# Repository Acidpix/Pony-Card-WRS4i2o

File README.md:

# Pony-Card-WRS4i2o

Pony-Card-WRS4i2o is a Wiegand/RS485 capable card for access controle powered by PoE

# Main feature 
  - Powered by PoE or 12V/2A input
  - Power sercurity device like badge reader in 12V/0.5A
  - Wiegand or RS485 input selectable by switch
  - In Wiegand mode, 1 digital output (e.g for drive 5V Led or buzzer from badge reader)   
  - 4 digital input (3V to 24V)
  - Drive 2 output NO/NC relay (230V/5A Max)
  - Can run on WiFi and/or Ethernet (e.g for failover)
  - Ready to Home assistant with EspHOME (Sample config avaliable)
  - Ready to MQTT with Tasmota (Base firmware avaliable)
  - -20C° +60C° running continous capability
  - Fit in DIN PLC Box like [this](https://fr.aliexpress.com/i/1005004933689728.html)
  - Dimention : 92.4mm X 87.5  

# Esp32 Pin Mapping 
  - GPIO 0 : Flash write mode Conected to CH340
  - GPIO 1 : UART_TX Conected to CH340
  - GPIO 2 : Free use in pin header
  - GPIO 3 : UART_RX Conected to CH340
  - GPIO 4 : Free use in pin header
  - GPIO 5 : Free use in pin header
  - GPIO 6 - 11 : Reserved by flash memory
  - GPIO 12 : Ethernet PHY Power
  - GPIO 13 : Wiegand D0 or RS485 RX
  - GPIO 14 : Wiegand D1 or RS485 TX
  - GPIO 15 : RS485 DIR or digital out in Wiegand mode (e.g for drive status LED on badge reader)
  - GPIO 16 : Free use in pin header
  - GPIO 17 : EMAC Clock out 180
  - GPIO 18 : MDIO(RMII)
  - GPIO 19 : EMAC TXD0(RMII)
  - GPIO 21 : EMAC TX Enable
  - GPIO 22 : EMAC TXD1(RMII)
  - GPIO 23 : MDC(RMII)
  - GPIO 25 : EMAC RXD0(RMII)
  - GPIO 26 : EMAC RXD1(RMII)
  - GPIO 27 : EMAC RX CRS DV
  - GPIO 32 : Relay 1
  - GPIO 33 : Relay 2
  - GPIO 34 : Digital Input 1 (3V - 24V)
  - GPIO 35 : Digital Input 2 (3V - 24V)
  - GPIO 36 : Digital Input 3 (3V - 24V)
  - GPIO 39 : Digital Input 4 (3V - 24V)

# Wiegand ESPHome example 

``` 
esphome:
  name: Pony Card WRS4i2o
  friendly_name: Pony_Card_WRS4i2o

esp32:
  board: esp32dev
  framework:
    type: arduino

# Enable logging
logger:

# Enable Home Assistant API
api:
  encryption:
    key: 

ota:
  password: 

ethernet:
  type: LAN8720
  mdc_pin: GPIO23
  mdio_pin: GPIO18
  clk_mode: GPIO17_OUT
  power_pin: GPIO12

globals:
  - id: autorized_badge
    type: int64_t
    restore_value: no
    initial_value: '5562314525698'

wiegand:
  - id: badgereader
    d0: GPIO13
    d1: GPIO14
    on_raw: 
      - if:
          condition:
            labda : 'return value == id(autorized_badge);
          then:
            - switch.toggle: r1
          else:
            - switch.toggle: r2
            - delay : 1s
            - switch.toggle: r2

binary_sensor:
  - platform: gpio
    pin: 
      number: 34
      inverted: true
    name: "input1"
  - platform: gpio
    pin: 
      number: 35
      inverted: true
    name: "input2"
  - platform: gpio
    pin: 
      number: 36
      inverted: true
    name: "input3"
  - platform: gpio
    pin: 
      number: 39
      inverted: true
    name: "input4"

output:
  - platform: gpio
    pin: 32
    id: 'Relay_1'  
  - platform: gpio
    pin: 33
    id: 'Relay_2'    

switch:
  - platform: output
    name: "Relay 1"
    id: "r1"
    output: 'Relay_1'
  - platform: output
    name: "Relay 2"
    id: "r2"
    output: 'Relay_2'
  - platform: gpio
    name: "LED"
    id: "led"
    pin:
      number: 15
      inverted: true 
``` 

# Misc
R49 was unpopulated resistance, because it's just for very old PoE device, support only type 1 PoE and this type need permanante 10mA current drain. But this produce 0.5w of heat and in certain condition make overhead the board, please populate only if your PoE injector dont work without an be careful of probaly over heating in +50C° environement.

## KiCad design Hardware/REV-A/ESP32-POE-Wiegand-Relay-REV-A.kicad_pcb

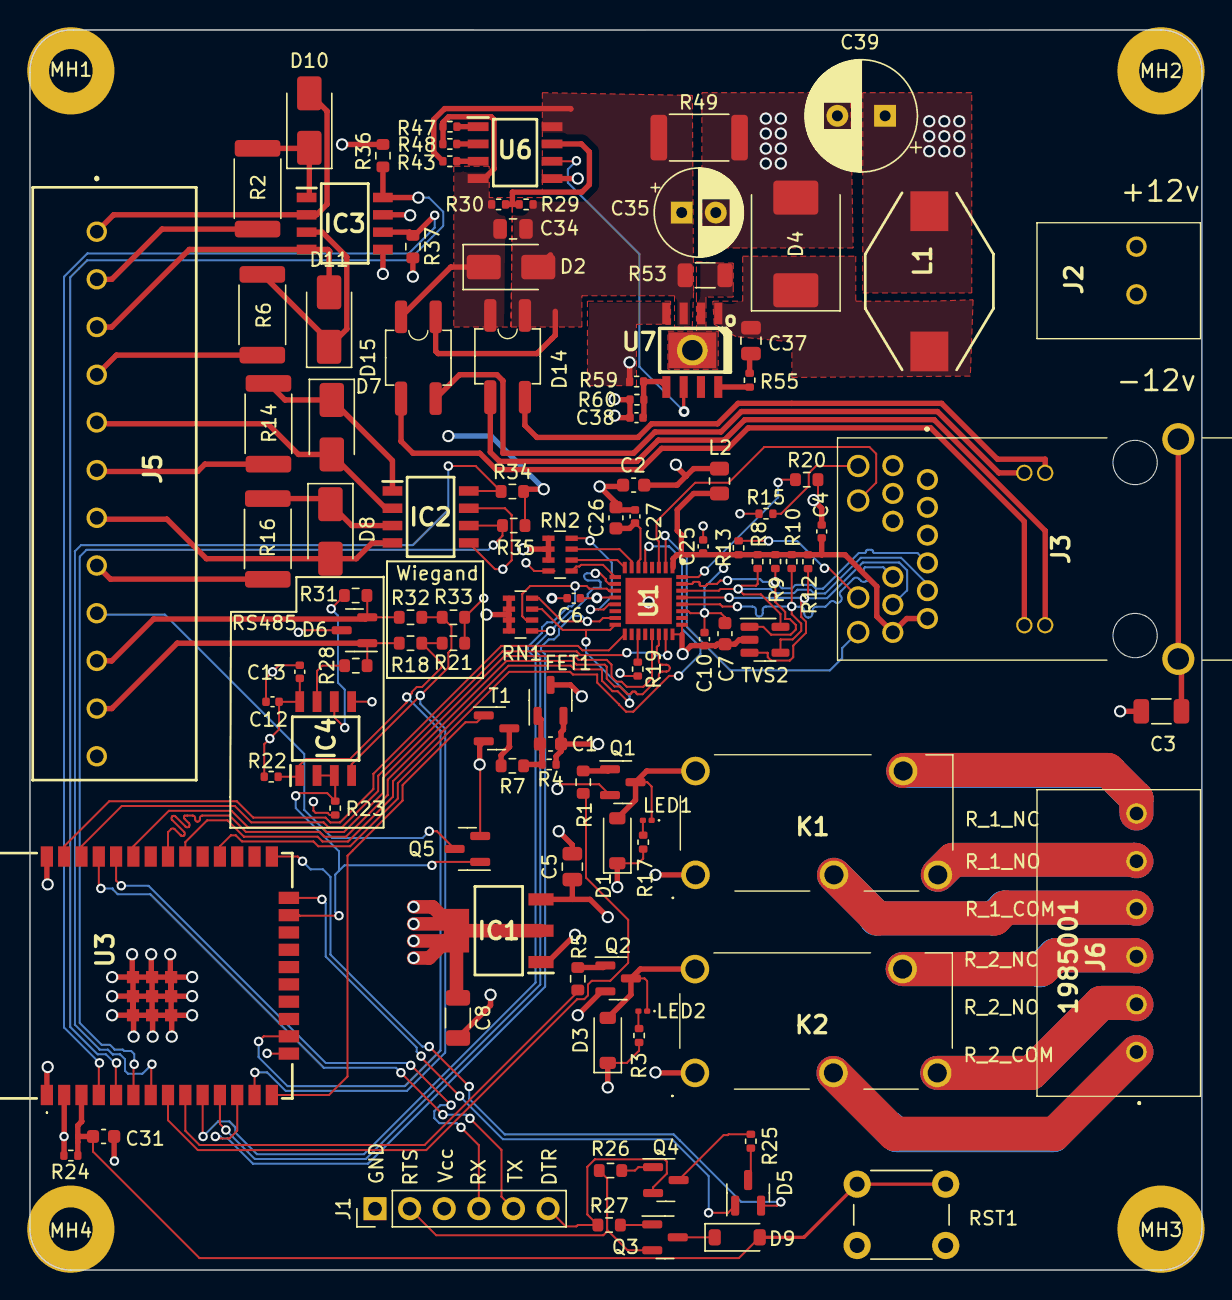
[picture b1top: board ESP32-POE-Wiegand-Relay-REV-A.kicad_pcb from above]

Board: 4 copper layers, 86.0 x 91.0 mm, 111 parts (0 on the bottom side), 99 nets.

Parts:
C1, C2, C7: 22uF/6.3V/20%/X5R/C0603; C_0603_1608Metric
C3: 1nF/2000V/10%/X7R/C1206; C_1206_3216Metric
C4, C6, C10, C12, C13, C25, C27: 100nF/16V/10%/X7R/C0402; C_0402_1005Metric
C5: 10uF/16v/10%/0805; C_0805_2012Metric
C8: 22uF/6.3v/10%/1206; C_1206_3216Metric
C26: 2.2uF/6.3V/10%/X5R/C0603; C_0603_1608Metric
C31: 1uF/10V/10%/X5R/C0603; C_0603_1608Metric
C34, C37: 100nF/100V/10%/X7R/C0805; C_0805_2012Metric
C35: 15uF/100V/20%/RM2.5/6.3x11mm(Farnell:1281844); CP_Radial_D6.3mm_P2.50mm
C38: 12pF/50V/5%/COG/C0402; C_0402_1005Metric
C39: 470uF/16V/20%/Low_ESR/RM3.5/8.0x15mm; CP_Radial_D8.0mm_P3.50mm
D1, D3, D9: 1N5819S4(SOD-123); D_SOD-123
D2: SMAJ58A/SMA; D_SMA
D4: SS510/100V/5A/0.85V/DO214AB(SMC); D_SMC
D5: BAT54C(SOT23-3); SOT-23
D6: STS232120B301; SOT-23
D7, D8, D10, D11: Diode 1KV; D_SMA
D14, D15: MDB10S YONG; SOP-4_3.8x4.1mm_P2.54mm_MB10S-YONG
FET1: WPM2015-3/TR; SOT-23-3
IC1: AZ1117CH-3.3TRG1; SOT230P700X180-4N
IC2, IC3: VOD207T; SOIC127P610X323-8N
IC4: THVD1420DR; SOIC127P600X175-8N
J1: Conn_01x06_MountingPin; PinHeader_1x06_P2.54mm_Vertical
J2: 1984963
J3: 0826-1X1T-GH-F; 08261X1TGHF
J5: 1985069
J6: 1985001
K1, K2: G5Q-1-DC12; G5Q1DC12
L1: DO3316P-333MLD; DO3316P333MLD
L2: FB0805/600R/2A; R_0805_2012Metric
LED1, LED2: LED/GREEN/0603; LED_0201_0603Metric
MH1, MH2, MH3, MH4: Mounting_hole_Shield_3.3mm; MountingHole_3.2mm_M3_Pad
Q1, Q2, Q3, Q4, Q5: BC817-40(SOT23); SOT-23
R1, R5, R7, R21, R26, R27, R33, R34, R35, R36, R37: 1k/R0603; R_0603_1608Metric
R2, R6, R14, R16: 1.2kR/5%/1W/2512/CR2512-JW-122ELF; R_2512_6332Metric
R3, R13, R15, R17: 2.2k/R0402; R_0402_1005Metric
R4, R19, R22, R23, R24, R30: 10k/R0402; R_0402_1005Metric
R8, R9, R10, R12: 49.9R/1%/R0402; R_0402_1005Metric
R18, R32: 470R/R0603; R_0603_1608Metric
R20: 12.1k/1%/R0603; R_0603_1608Metric
R25: 220R/R0402; R_0402_1005Metric
R28, R31: 10R/5%/pulse resistor/0603; R_0603_1608Metric
R29: 130k/R0402; R_0402_1005Metric
R43: 24.9k/1%/R0402; R_0402_1005Metric
R47: 180k/1%/R0402; R_0402_1005Metric
R48: 4.42k/1%/1/16W/R0402; R_0402_1005Metric
R49: 4.7k/R2512; R_2512_6332Metric
R53: 0.03R/1%/R1206; R_1206_3216Metric
R55: 4.7R/R0402; R_0402_1005Metric
R59: 21k/1%/R0402; R_0402_1005Metric
R60: 300k/1%/R0402; R_0402_1005Metric
RN1, RN2: 2.2k/5%/0603x4; R_Array_Concave_4x0603
RST1: T1107A(6x3,8x2,5MM); SW_PUSH_6mm
T1: LMUN2211LT1G(SOT-23); SOT-23
TVS2: ESDS314DBVR(SOT-23-5); SOT-23-5
U1: LAN8710A-EZC(QFN32); QFN50P500X500X100-33N-D
U3: ESP-WROOM-32; ESP32WROOM32EN4
U6: TPS2376DDAR-H (SO-8); SOIC127P600X175-8N
U7: TX4138(ESOIC-8); SOIC8E

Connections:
+3.3V: C1.1, C8.1, C12.2, C13.2, FET1.2, IC1.2 (OUTPUT), IC1.4 (VOUT), IC4.8 (VCC), J1.3, R4.1, R22.1, R24.1, R34.2, R35.2, R36.2, R37.2, U3.2 (3V3)
+3V3: C2.1, C6.1, FET1.3, L2.1, R19.2, RN1.5 (R4_2), RN1.6 (R3_2), RN1.7 (R2_2), RN1.8 (R1_2), RN2.8 (R1_2), U1.12 (VDDIO)
+12V: C5.1, C38.1, C39.1, D1.1 (K), D3.1 (K), IC1.3 (INPUT), J2.1, K1.1 (COIL_1), K2.1 (COIL_1), L1.2, R3.2, R17.2, R60.1
/+Input1: J5.8, R16.1
/+Input2: J5.6, R14.1
/+Input3: J5.4, R6.1
/+Input4: J5.2, R2.1
/-Input1: D8.2 (A), IC2.4 (C_2), J5.7
/-Input2: D7.2 (A), IC2.2 (C_1), J5.5
/-Input3: D11.2 (A), IC3.4 (C_2), J5.3
/-Input4: D10.2 (A), IC3.2 (C_1), J5.1
/D_Com: D5.3, R25.1
/ESP_EN: C31.2, D9.2 (A), R24.2, RST1.1, U3.3 (EN)
/GPI34/Input1: IC2.6 (C_3), R35.1, U3.6 (GPI34/ADC1_CH6/RTC_GPIO4)
/GPI35/Input2: IC2.8 (C_4), R34.1, U3.7 (GPI35/ADC1_CH7/RTC_GPIO5)
/GPI36/Input3: IC3.6 (C_3), R37.1, U3.4 (GPI36/SENSOR_VP/ADC_H/ADC1_CH0/RTC_GPIO0)
/GPI39/Input4: IC3.8 (C_4), R36.1, U3.5 (GPI39/SENSOR_VN/ADC1_CH3/ADC_H/RTC_GPIO3)
/GPIO0: D5.2, U3.25 (GPIO0/ADC2_CH1/TOUCH1/RTC_GPIO11/CLK_OU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)
/GPIO1/UART_TX0: J1.5, U3.35 (GPIO1/U0TXD/CLK_OUT3/EMAC_RXD2)
/GPIO2: D5.1, U3.24 (GPIO2/ADC2_CH2/TOUCH2/RTC_GPIO12/HSPIWP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)
/GPIO3/UART_RX0: J1.4, U3.34 (GPIO3/U0RXD/CLK_OUT2)
/GPIO12/PHY_PWR: T1.1 (B), U3.14 (GPIO12/ADC2_CH5/TOUCH5/RTC_GPIO15/MTDI/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)
/GPIO13/Wiegand_D0/RS485_RX: IC4.1 (R), R18.2, R21.2, R22.2, U3.16 (GPIO13/ADC2_CH4/TOUCH4/RTC_GPIO14/MTCK/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)
/GPIO14/Wiegand_D1/RS485_TX: IC4.4 (D), R32.2, R33.2, U3.13 (GPIO14/ADC2_CH6/TOUCH6/RTC_GPIO16/MTMS/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)
/GPIO15/Wiegand_LED/RS485_DIR: IC4.2 (~RE), IC4.3 (DE), Q5.1 (B), R23.1, U3.23 (GPIO15/ADC2_CH3/TOUCH3/MTDO/HSPICS0/RTC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)
/GPIO17/EMAC_CLK_OUT_180: U1.5 (XTAL1/CLKIN), U3.28 (GPIO17/HS1_DATA5/U2TXD/EMAC_CLK_OUT_180)
/GPIO18/MDIO(RMII): RN1.3 (R3_1), U1.16 (MDIO), U3.30 (GPIO18/VSPICLK/HS1_DATA7)
/GPIO19/EMAC_TXD0(RMII): U1.22 (TXD0), U3.31 (GPIO19/VSPIQ/U0CTS/EMAC_TXD0)
/GPIO21/EMAC_TX_EN(RMII): U1.21 (TXEN), U3.33 (GPIO21/VSPIHD/EMAC_TX_EN)
/GPIO22/EMAC_TXD1(RMII): U1.23 (TXD1), U3.36 (GPIO22/VSPIWP/U0RTS/EMAC_TXD1)
/GPIO23/MDC(RMII): U1.17 (MDC), U3.37 (GPIO23/VSPID/HS1_STROBE)
/GPIO25/EMAC_RXD0(RMII): RN1.2 (R2_1), U1.11 (RXD0/MODE0), U3.10 (GPIO25/DAC_1/ADC2_CH8/RTC_GPIO6/EMAC_RX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)
/GPIO26/EMAC_RXD1(RMII): RN1.1 (R1_1), U1.10 (RXD1/MODE1), U3.11 (GPIO26/DAC_2/ADC2_CH9/RTC_GPIO7/EMAC_RX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)
/GPIO27/EMAC_RX_CRS_DV: RN1.4 (R4_1), U1.15 (COL/CRS_DV/MODE2), U3.12 (GPIO27/ADC2_CH7/TOUCH7/RTC_GPIO17/EMAC_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)
/GPIO32/REL1: R1.1, U3.8 (GPIO32/XTAL_32K_P/ADC1_CH4/TOUCH9/RTC_G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)
/GPIO33/REL2: R5.1, U3.9 (GPIO33/XTAL_32K_N/ADC1_CH5/TOUCH8/RTC_G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)
/RD+: J3.4 (TRD2+), R9.1, TVS2.1 (I/O1), U1.31 (RXP)
/RD-: J3.5 (TRD2-), R8.1, TVS2.5 (I/O4), U1.30 (RXN)
/Relay_1_COM: J6.4, K1.2 (COM)
/Relay_1_NC: J6.6, K1.4 (NC)
/Relay_1_NO: J6.5, K1.3 (NO)
/Relay_2_COM: J6.1, K2.2 (COM)
/Relay_2_NC: J6.3, K2.4 (NC)
/Relay_2_NO: J6.2, K2.3 (NO)
/TD+: J3.11 (TRD1+), R12.1, TVS2.3 (I/O2), U1.29 (TXP)
/TD-: J3.10 (TRD1-), R10.1, TVS2.4 (I/O3), U1.28 (TXN)
/Wiegand_D0/RS485_A: D6.1 (K), J5.11, R18.1, R28.2
/Wiegand_D1/RS485_B: D6.2 (K), J5.10, R31.2, R32.1
/Wiegand_LED: J5.9, Q5.3 (C)
GND: C2.2, C3.1, C4.2, C5.2, C6.2, C7.2, C8.2, C10.2, C12.1, C13.1, C25.2, C26.2, C27.2, C31.1, C35.2, C39.2, D4.2 (A), D6.3 (A), IC1.1 (ADJ/GND), IC2.5 (E_1), IC2.7 (E_2), IC3.5 (E_1), IC3.7 (E_2), IC4.5 (GND), J1.1, J2.2, J5.12, MH1.1 (GND1), MH2.1 (GND1), MH3.1 (GND1), MH4.1 (GND1), Q1.2 (E), Q2.2 (E), Q5.2 (E), R15.2, R20.2, R21.1, R23.2, R33.1, R49.2, R59.2, RN2.5 (R4_2), RN2.6 (R3_2), RN2.7 (R2_2), RST1.2, T1.2 (E), TVS2.2 (GND), U1.24 (TXD2), U1.25 (TXD3), U1.33 (GND), U3.1 (GND), U3.15 (GND), U3.38 (GND), U3.39 (THERMAL_PAD), U3.40 (40_GND), U3.41 (41_GND), U3.42 (42_GND), U3.43 (43_GND), U3.44 (44_GND), U3.45 (45_GND), U3.46 (46_GND), U3.47 (47_GND), U6.5 (RTN), U7.4 (GND)
unnamed: C1.2, FET1.1, R4.2, R7.2
unnamed: C3.2, J3.MH1, J3.MH2
unnamed: C37.2, R55.2
unnamed: D1.2 (A), K1.5 (COIL_2), LED1.1 (K), Q1.3 (C)
unnamed: D3.2 (A), K2.5 (COIL_2), LED2.1 (K), Q2.3 (C)
unnamed: C37.1, D4.1 (K), L1.1, U7.1 (SW)
unnamed: D7.1 (K), IC2.1 (A_1), R14.2
unnamed: D8.1 (K), IC2.3 (A_2), R16.2
unnamed: D9.1 (K), Q3.3 (C)
unnamed: D10.1 (K), IC3.1 (A_1), R2.2
unnamed: D11.1 (K), IC3.3 (A_2), R6.2
unnamed: IC4.6 (A), R31.1
unnamed: IC4.7 (B), R28.1
unnamed: J1.2, Q3.2 (E), R26.1
unnamed: J1.6, Q4.2 (E), R27.1
unnamed: J3.19 (LED_G+), R13.1
unnamed: J3.20 (LED_G-), U1.2 (LED2/NINTSEL)
unnamed: J3.18 (LED_Y+), U1.3 (LED1/REGOFF)
unnamed: J3.17 (LED_Y-), R15.1
unnamed: C4.1, C7.1, C10.1, C25.1, J3.6 (TRCT2), J3.12 (TRCT1), L2.2, R8.2, R9.2, R10.2, R12.2, R13.2, U1.1 (VDD2A), U1.27 (VDD1A)
unnamed: D15.2, J3.13 (VC1)
unnamed: D15.1, J3.14 (VC2)
unnamed: D14.2, J3.15 (VC3)
unnamed: D14.1, J3.16 (VC4)
unnamed: LED1.2 (A), R17.1
unnamed: LED2.2 (A), R3.1
unnamed: Q1.1 (B), R1.2
unnamed: Q2.1 (B), R5.2
unnamed: Q3.1 (B), R27.2
unnamed: Q4.1 (B), R26.2
unnamed: Q4.3 (C), R25.2
unnamed: R53.1, U7.2 (ILIM), U7.9 (ILIM)
unnamed: RN2.1 (R1_1), U1.9 (RXD2/RMIISEL)
unnamed: RN2.2 (R2_1), U1.8 (RXD3/PHYAD2)
unnamed: RN2.3 (R3_1), U1.7 (RXCLK/PHYAD1)
unnamed: RN2.4 (R4_1), U1.13 (RXER/RXD4/PHYAD0)
unnamed: R7.1, T1.3 (C)
unnamed: R19.1, U1.19 (NRST)
unnamed: R20.1, U1.32 (RBIAS)
unnamed: C26.1, C27.1, U1.6 (VDDCR)
unnamed: R48.2, U6.2 (CLASS)
unnamed: R43.2, U6.3 (DET)
unnamed: R47.2, U6.1 (ILIM)
unnamed: R29.2, R30.1, U6.7 (NC/UVLO)
unnamed: U6.6 (PG), U7.6 (EN)
unnamed: R55.1, U7.8 (BS)
unnamed: C38.2, R59.1, R60.2, U7.5 (FB)
Spare1: C34.1, C35.1, D2.2 (A2), D14.3 (+), D15.3 (+), R29.1, R43.1, R49.1, R53.2, U6.8 (VDD), U7.3 (Vin)
Spare2: C34.2, D2.1 (A1), D14.4 (-), D15.4 (-), R30.2, R47.1, R48.1, U6.4 (VSS)

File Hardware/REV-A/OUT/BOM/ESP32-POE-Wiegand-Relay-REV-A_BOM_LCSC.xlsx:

Reference(s) | Value | Footprint | LCSC/JLC Part Number | Mouser Part Number | Qty
C1, C2, C7 | 22uF/6.3V/20%/X5R/C0603 | Capacitor_SMD:C_0603_1608Metric | C2991805 | 81-GRM188R60J226ME0D | 3
C3 | 1nF/2000V/10%/X7R/C1206 | Capacitor_SMD:C_1206_3216Metric | C725573 | 710-885342208024 | 1
C4, C6, C10, C12, C13, C25, C27 | 100nF/16V/10%/X7R/C0402 | Capacitor_SMD:C_0402_1005Metric | C1525 | 81-GRM155R71C104KA8J | 7
C5 | 10uF/16v/10%/0805 | Capacitor_SMD:C_0805_2012Metric | C318695 | 187-CL21A106KOCLRNC | 1
C8 | 22uF/6.3v/10%/1206 | Capacitor_SMD:C_1206_3216Metric | C444887 | 187-CL31X226KQHNNNE | 1
C26 | 2.2uF/6.3V/10%/X5R/C0603 | Capacitor_SMD:C_0603_1608Metric | C412627 | 81-GCM188R70J225KE2D | 1
C31 | 1uF/10V/10%/X5R/C0603 | Capacitor_SMD:C_0603_1608Metric | C3000819 | 77-VJ0603Y105KXQCWBC | 1
C34, C37 | 100nF/100V/10%/X7R/C0805 | Capacitor_SMD:C_0805_2012Metric | C2174642 | 810-C2012X7R2A104K | 2
C38 | 12pF/50V/5%/COG/C0402 | Capacitor_SMD:C_0402_1005Metric | C386126 | 963-UMK105CG120JVHF | 1
D1, D3 | 1N5819S4(SOD-123) | Diode_SMD:D_SOD-123 | C123003 | 621-1N5819HW-F | 2
D2 | SMAJ58A/SMA | Diode_SMD:D_SMA | C151246 | 576-SMAJ58A | 1
D4 | SS510/100V/5A/0.85V/DO214AB(SMC) | Diode_SMD:D_SMC | C2985020 | 750-SS510C-HF | 1
D5 | BAT54C(SOT23-3) | Package_TO_SOT_SMD:SOT-23 | C14308 | 863-BAT54CLT1G | 1
D6 | STS232120B301 | Package_TO_SOT_SMD:SOT-23 | C2985651 | 947-SM712.TCT | 1
D7, D8, D10, D11 | Diode 1KV | Diode_SMD:D_SMA | C2909831 |  | 4
D9 | 1N5819S4(SOD-123) | Diode_SMD:D_SOD-123 | C123003 | 621-1N5819HW-F | 1
D14, D15 | MDB10S YONG | SamacSys_Parts:SOP-4_3.8x4.1mm_P2.54mm_MB10S-YONG | C2892569 |  | 2
FET1 | WPM2015-3/TR | Package_TO_SOT_SMD:SOT-23-3 | C6562215 | 637-MMFTP3401 | 1
IC1 | AZ1117CH-3.3TRG1 | SamacSys_Parts:SOT230P700X180-4N | C92102 | 621-AZ1117CH-3.3TRG1 | 1
IC2, IC3 | VOD207T | SamacSys_Parts:SOIC127P610X323-8N | C146234 | 78-VOD207T | 2
IC4 | THVD1420DR | SamacSys_Parts:SOIC127P600X175-8N | C3235215 | 595-THVD1420DR | 1
L1 | DO3316P-333MLD | SamacSys_Parts:DO3316P333MLD | C108313 | 994-DO3316P-333MLD | 1
L2 | FB0805/600R/2A | Resistor_SMD:R_0805_2012Metric | C81034 | 810-MPZ2012S601ATD25 | 1
LED1, LED2 | LED/GREEN/0603 | LED_SMD:LED_0201_0603Metric | C2962098 | 710-150060VS75000 | 2
Q1, Q2, Q3, Q4, Q5 | BC817-40(SOT23) | Package_TO_SOT_SMD:SOT-23 | C146798 | 637-BC817-40 | 5
R1, R5, R7, R21, R26, R27, R33, R34, R35, R36, R37 | 1k/R0603 | Resistor_SMD:R_0603_1608Metric | C73797 | 652-CR0603AFX1001ELF | 11
R2, R6, R14, R16 | 1.2kR/5%/1W/2512/CR2512-JW-122ELF | Resistor_SMD:R_2512_6332Metric | C2974106 | 652-CR2512-JW-122ELF | 4
R3, R13, R15, R17 | 2.2k/R0402 | Resistor_SMD:R_0402_1005Metric | C4202009 | 71-CRCW04022K20JNEDC | 4
R4, R19, R22, R23, R24, R30 | 10k/R0402 | Resistor_SMD:R_0402_1005Metric | C3020235 | 71-RCS040210K0FKED | 6
R8, R9, R10, R12 | 49.9R/1%/R0402 | Resistor_SMD:R_0402_1005Metric | C854345 | 667-ERJ-2RKF49R9X | 4
R18, R32 | 470R/R0603 | Resistor_SMD:R_0603_1608Metric | C844564 | 71-CRCW0603470RFKEAC | 2
R20 | 12.1k/1%/R0603 | Resistor_SMD:R_0603_1608Metric | C2930059 | 652-CR0603FX-1212ELF | 1
R25 | 220R/R0402 | Resistor_SMD:R_0402_1005Metric | C284422 | 652-CR0402JW-221GLF | 1
R28, R31 | 10R/5%/pulse resistor/0603 | Resistor_SMD:R_0603_1608Metric | C319920 | 279-CPF0603F10RC1 | 2
R29 | 130k/R0402 | Resistor_SMD:R_0402_1005Metric | C102797 | 652-CR0402FX-1303GLF | 1
R43 | 24.9k/1%/R0402 | Resistor_SMD:R_0402_1005Metric | C852664 | 652-CR0402FX-2492GLF | 1
R47 | 180k/1%/R0402 | Resistor_SMD:R_0402_1005Metric | C364850 | 652-CR0402FX-1803GLF | 1
R48 | 4.42k/1%/1/16W/R0402 | Resistor_SMD:R_0402_1005Metric | C103045 | 652-CR0402-FX4421GLF | 1
R49 | 4.7k/R2512 | Resistor_SMD:R_2512_6332Metric | C269368 | 652-CR2512-JW-472ELF | 1
R53 | 0.03R/1%/R1206 | Resistor_SMD:R_1206_3216Metric | C875624 | 71-WSL1206R0300FEA | 1
R55 | 4.7R/R0402 | Resistor_SMD:R_0402_1005Metric | C514781 | 652-CR0402-J/-4R7GLF | 1
R59 | 21k/1%/R0402 | Resistor_SMD:R_0402_1005Metric | C2692912 | 652-CR0402-FX2102GLF | 1
R60 | 300k/1%/R0402 | Resistor_SMD:R_0402_1005Metric | C364989 | 652-CR0402-JW-304GLF | 1
RN1, RN2 | 2.2k/5%/0603x4 | Resistor_SMD:R_Array_Concave_4x0603 | C102658 | 652-CAT16A-222J4LF | 2
RST1 | T1107A(6x3,8x2,5MM) | Button_Switch_THT:SW_PUSH_6mm | C97440 |  | 1
T1 | LMUN2211LT1G(SOT-23) | Package_TO_SOT_SMD:SOT-23 | C12775 |  | 1
TVS2 | ESDS314DBVR(SOT-23-5) | Package_TO_SOT_SMD:SOT-23-5 | C1847859 | 595-ESDS314DBVR | 1
U1 | LAN8710A-EZC(QFN32) | SamacSys_Parts:QFN50P500X500X100-33N-D | C46185 | 886-LAN8710A-EZC-TR | 1
U6 | TPS2376DDAR-H (SO-8) | SamacSys_Parts:SOIC127P600X175-8N | C544899 | 595-TPS2376D | 1
U7 | TX4138(ESOIC-8) | SamacSys_Parts:SOIC8E | C329267 |  | 1

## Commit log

2024-01-12 Cleanup
2024-01-12 update BOM
2024-01-12 README update
2024-01-12 Readme
2024-01-12 logo update
2024-01-12 Create LICENSE-CC-BY-SA
2024-01-13 Update Bornier
2024-01-18 Changer Ethernet Connector, add Switch Wiegand/RS485
